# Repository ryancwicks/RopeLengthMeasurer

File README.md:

# RopeLengthMeasurer
Tool for measuring long lengths of rope and cable.

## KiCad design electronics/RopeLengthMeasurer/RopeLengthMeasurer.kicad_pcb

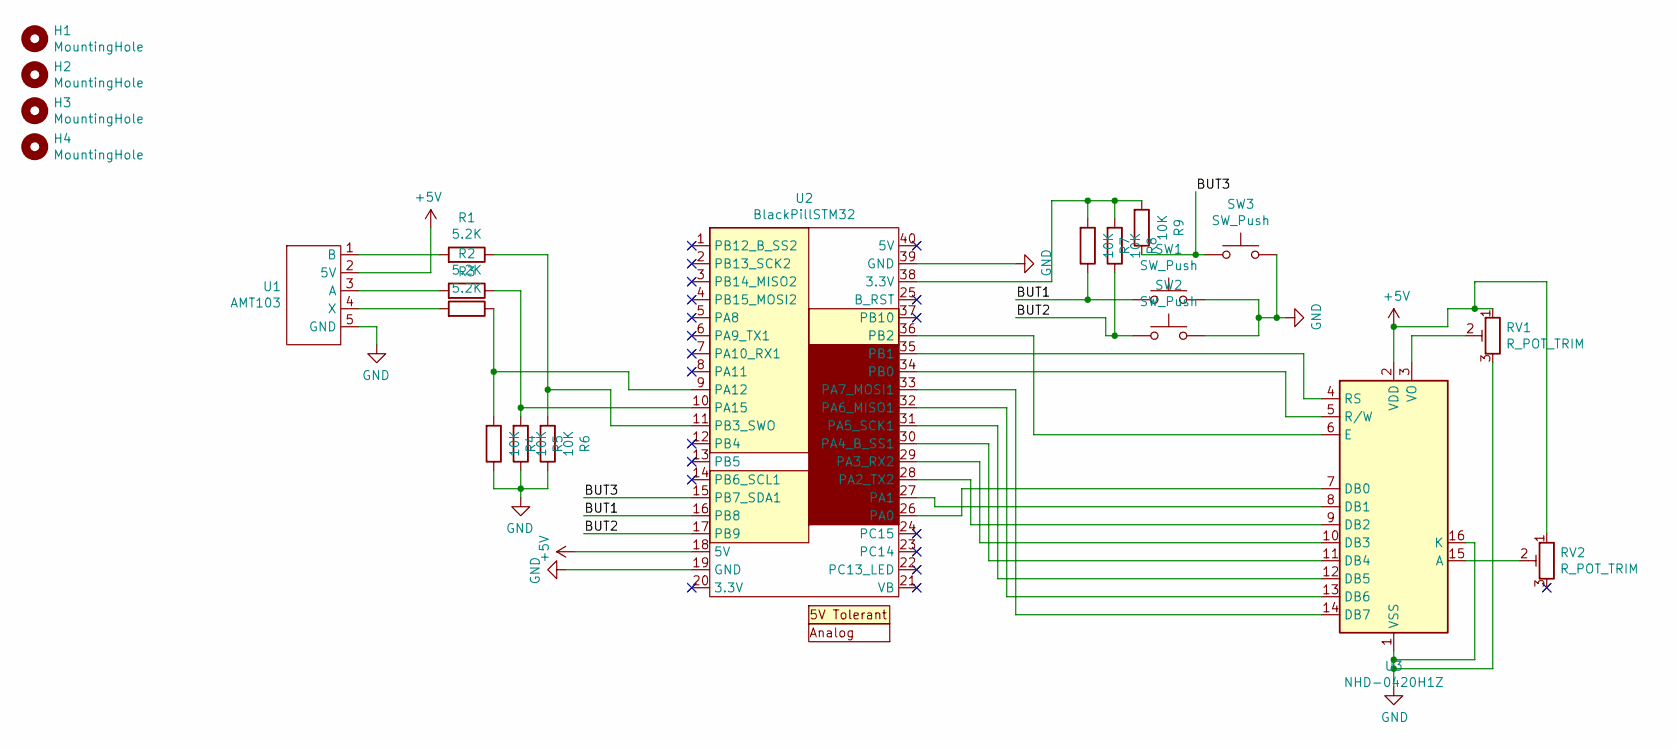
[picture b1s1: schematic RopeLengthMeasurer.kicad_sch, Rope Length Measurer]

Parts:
H1, H2, H3, H4: MountingHole; MountingHole_3.2mm_M3
R1, R2, R3: 5.2K; R_0603_1608Metric_Pad1.05x0.95mm_HandSolder
R4, R5, R6, R7, R8, R9: 10K; R_0603_1608Metric_Pad1.05x0.95mm_HandSolder
RV1, RV2: R_POT_TRIM; Potentiometer_Piher_PT-10-V10_Vertical
SW1, SW2, SW3: SW_Push; SW_PUSH_6mm_H5mm
U1: AMT103; PinHeader_1x05_P2.54mm_Vertical
U2: BlackPillSTM32; BlackPill
U3: NHD-0420H1Z; WC1602A

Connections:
+5V: RV1.1, RV2.1, U1.2 (5V), U2.18 (5V), U3.2 (VDD)
/BUT1: R7.1, SW1.1, U2.16 (PB8)
/BUT2: R8.1, SW2.1, U2.17 (PB9)
/BUT3: R9.1, SW3.1, U2.15 (PB7_SDA1)
GND: R4.1, R5.1, R6.1, RV1.3, SW1.2, SW2.2, SW3.2, U1.5 (GND), U2.19 (GND), U2.39 (GND), U3.1 (VSS), U3.16 (K)
unnamed: R1.1, R6.2, U2.11 (PB3_SWO)
unnamed: R1.2, U1.1 (B)
unnamed: R2.1, R5.2, U2.10 (PA15)
unnamed: R2.2, U1.3 (A)
unnamed: R3.1, R4.2, U2.9 (PA12)
unnamed: R3.2, U1.4 (X)
unnamed: R7.2, R8.2, R9.2, U2.38 (3.3V)
unnamed: RV1.2, U3.3 (VO)
unnamed: RV2.2, U3.15 (A)
unnamed: U2.26 (PA0), U3.7 (DB0)
unnamed: U2.27 (PA1), U3.8 (DB1)
unnamed: U2.28 (PA2_TX2), U3.9 (DB2)
unnamed: U2.29 (PA3_RX2), U3.10 (DB3)
unnamed: U2.30 (PA4_B_SS1), U3.11 (DB4)
unnamed: U2.31 (PA5_SCK1), U3.12 (DB5)
unnamed: U2.32 (PA6_MISO1), U3.13 (DB6)
unnamed: U2.33 (PA7_MOSI1), U3.14 (DB7)
unnamed: U2.34 (PB0), U3.5 (R/W)
unnamed: U2.35 (PB1), U3.4 (RS)
unnamed: U2.36 (PB2), U3.6 (E)

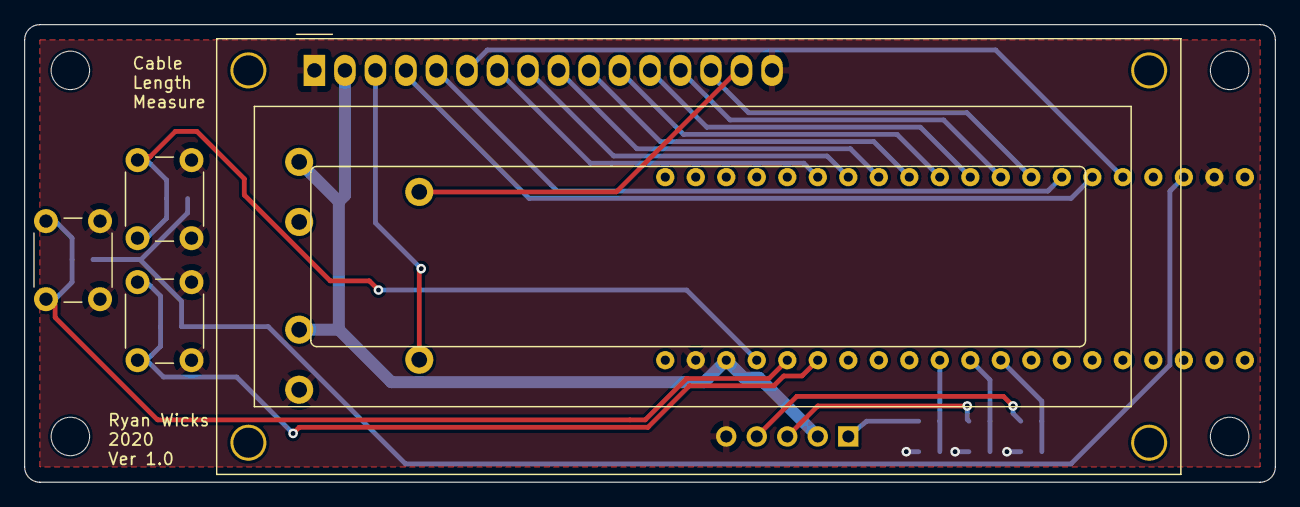
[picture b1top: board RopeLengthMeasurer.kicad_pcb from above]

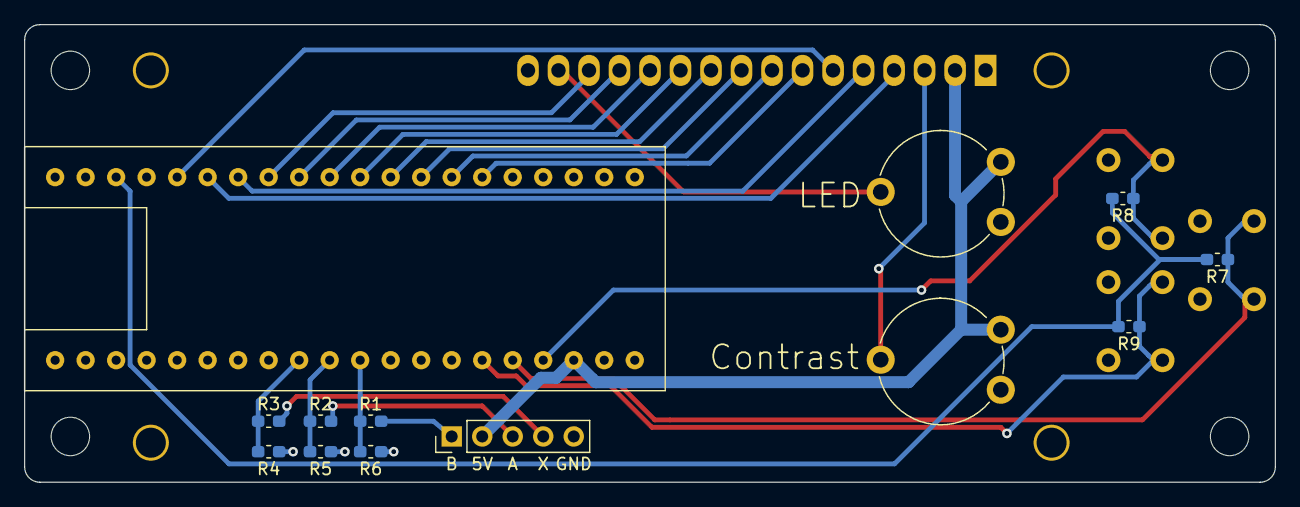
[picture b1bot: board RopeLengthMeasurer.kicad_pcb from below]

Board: 2 copper layers, 104.1 x 38.1 mm, 21 parts (13 on the bottom side), 25 nets.

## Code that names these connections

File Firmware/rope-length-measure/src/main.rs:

//! Blinks an LED
//! 
//! Measures the length of a rope run over a quaderature encoder and displays the result on a HD44780 compatible LED display.
#![no_main]
#![no_std]

// Halt on panic
#[allow(unused_extern_crates)] // NOTE(allow) bug rust-lang/rust#53964
extern crate panic_halt; // panic handler

use core::cell::{Cell, RefCell};

use cortex_m;
use cortex_m_rt::entry;
use cortex_m::interrupt::{free, CriticalSection, Mutex};
use core::ops::DerefMut;
//use cortex_m::asm::delay;
//use ufmt::uwrite;
use core::fmt::Write;
use heapless::String;
use heapless::consts::*;
use embedded_hal::Direction as RotaryDirection;

use stm32f4xx_hal as hal;
use crate::hal::{prelude::*, 
                interrupt,
                gpio::{gpiob::PB8, Edge, ExtiPin, Input, Floating},
                stm32,
                qei::Qei};

mod display;
mod counted_length;

//static QUAD_A: Mutex<RefCell<Option<PA11<Input<Floating>>>>> = Mutex::new(RefCell::new(None));
//static QUAD_B: Mutex<RefCell<Option<PA12<Input<Floating>>>>> = Mutex::new(RefCell::new(None));
//static COUNT: Mutex<Cell<i32>> = Mutex::new(Cell::new(0));
//static OLD_STATE: Mutex<Cell<bool>> = Mutex::new(Cell::new(false));
static RESET_COUNTER: Mutex<Cell<bool>> = Mutex::new(Cell::new(false));
static BUT1: Mutex<RefCell<Option<PB8<Input<Floating>>>>> = Mutex::new(RefCell::new(None));

#[entry]
fn main() -> ! {
    if let (Some(mut dp), Some(cp)) = (
        stm32::Peripherals::take(),
        cortex_m::peripheral::Peripherals::take(),
    ) {
        dp.RCC.apb2enr.write(|w| w.syscfgen().enabled());
        // Set up the system clock. We want to run at 48MHz for this one.
        let rcc = dp.RCC.constrain();
        let clocks = rcc.cfgr.sysclk(48.mhz()).freeze();
        let mut hal_delay = hal::delay::Delay::new(cp.SYST, clocks);

        // Set up the ports
        let gpioa = dp.GPIOA.split();
        let gpiob = dp.GPIOB.split();
        let gpioc = dp.GPIOC.split();

        // Set up the LED.
        let mut led = gpioc.pc13.into_push_pull_output();
        led.set_high().unwrap();

        // Set up the GPIO pins
        let mut a_pin = gpioa.pa15.into_push_pull_output();
        a_pin.set_low().unwrap();
        let mut b_pin = gpiob.pb3.into_push_pull_output();
        b_pin.set_low().unwrap();
        let mut but1 = gpiob.pb8.into_floating_input(); //mid button

        let _but2 = gpiob.pb9.into_floating_input(); //up button
        let _but3 = gpiob.pb7.into_floating_input(); //down button
        let rotary_encoder_pins = (
            a_pin.into_alternate_af1(),
            b_pin.into_alternate_af1()
        );
        

        let rotary_encoder_timer = dp.TIM2;
        let rotary_encoder = Qei::tim2(rotary_encoder_timer, rotary_encoder_pins);

        but1.make_interrupt_source(&mut dp.SYSCFG);
        but1.enable_interrupt(&mut dp.EXTI);
        but1.trigger_on_edge (&mut dp.EXTI, Edge::FALLING);

        free(|cs| {
            BUT1.borrow(cs).replace(Some(but1));
        });

        // Enable interrupts
        stm32::NVIC::unpend(hal::stm32::Interrupt::EXTI9_5);
        unsafe {
            stm32::NVIC::unmask(hal::stm32::Interrupt::EXTI9_5);
        };
        

        //Set up the display pins
        let d0 = gpioa.pa0.into_push_pull_output().downgrade();
        let d1 = gpioa.pa1.into_push_pull_output().downgrade();
        let d2 = gpioa.pa2.into_push_pull_output().downgrade();
        let d3 = gpioa.pa3.into_push_pull_output().downgrade();
        let d4 = gpioa.pa4.into_push_pull_output().downgrade();
        let d5 = gpioa.pa5.into_push_pull_output().downgrade();
        let d6 = gpioa.pa6.into_push_pull_output().downgrade();
        let d7 = gpioa.pa7.into_push_pull_output().downgrade();
        let enable_pin = gpiob.pb2.into_push_pull_output().downgrade();
        let read_write_pin = gpiob.pb1.into_push_pull_output().downgrade();
        let register_select_pin = gpiob.pb0.into_push_pull_output().downgrade();

        let data_bus: [stm32f4xx_hal::gpio::gpioa::PA<stm32f4xx_hal::gpio::Output<stm32f4xx_hal::gpio::PushPull>>; 8] = [d0, d1, d2, d3, d4, d5, d6, d7];   

        let mut display = display::Display::new(data_bus, enable_pin, read_write_pin, register_select_pin, clocks.hclk() );
        display.initialize_display();

        display.set_cursor_position(0, 0).unwrap();
        display.write_str("Length:");
        display.set_cursor_position(1, 0).unwrap();
        display.write_str("0 m");
        
        let mut current_count = rotary_encoder.count();
        let mut length = counted_length::CountedLength::new(0.01, 2048);
        loop {
            
            let reset_count = free(|cs| RESET_COUNTER.borrow(cs).get());
            
            let new_count = rotary_encoder.count();

            if (new_count != current_count) || (reset_count) {

                if reset_count {
                    free(|cs| RESET_COUNTER.borrow(cs).replace(false));
                    length.reset();
                } else {
                    let diff = new_count as i32 - current_count as i32;  
                    current_count = new_count;  
                    length.update_with_difference(diff);

                    // Light up the LED when turning clockwise, turn it off
                    // when turning counter-clockwise.
                    match rotary_encoder.direction() {
                        RotaryDirection::Upcounting => {
                            led.set_low().unwrap();
                        },
                        RotaryDirection::Downcounting => {
                            led.set_high().unwrap();
                        },
                    }
                }

                let mut count_str = String::<U15>::new();
                let _ = write!(count_str, "{:.3} m", length.get_length());
                display.set_cursor_position(1, 0).unwrap();
                for _ in 0..count_str.len()+1 {
                    display.write_str(" ");
                }
                display.set_cursor_position(1, 0).unwrap();
                display.write_str(count_str.as_str());
            }
    
            hal_delay.delay_ms(10_u32);         
        }
    }

    loop {}
}


#[interrupt]
fn EXTI9_5(){
    free(|cs| {
        let mut btn_ref = BUT1.borrow(cs).borrow_mut();
        if let Some(ref mut btn) = btn_ref.deref_mut() {
            // We cheat and don't bother checking _which_ exact interrupt line fired - there's only
            // ever going to be one in this example.
            btn.clear_interrupt_pending_bit();
            RESET_COUNTER.borrow(cs).replace(true);
        }
    });
}

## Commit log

2020-09-25 Added simple gitignore file.
2020-09-27 Switching design to black pill.
2020-10-01 Finished coding an implementation of the newhaven display module.
2020-10-22 Display working. Debugging sort of working.
2020-10-23 Reader and screen working, in process of moving logic to interrupt.
2020-10-25 Got reader working with quaderature encoder interface.
2020-11-01 Software working with new circuit board. Reset button also working.
